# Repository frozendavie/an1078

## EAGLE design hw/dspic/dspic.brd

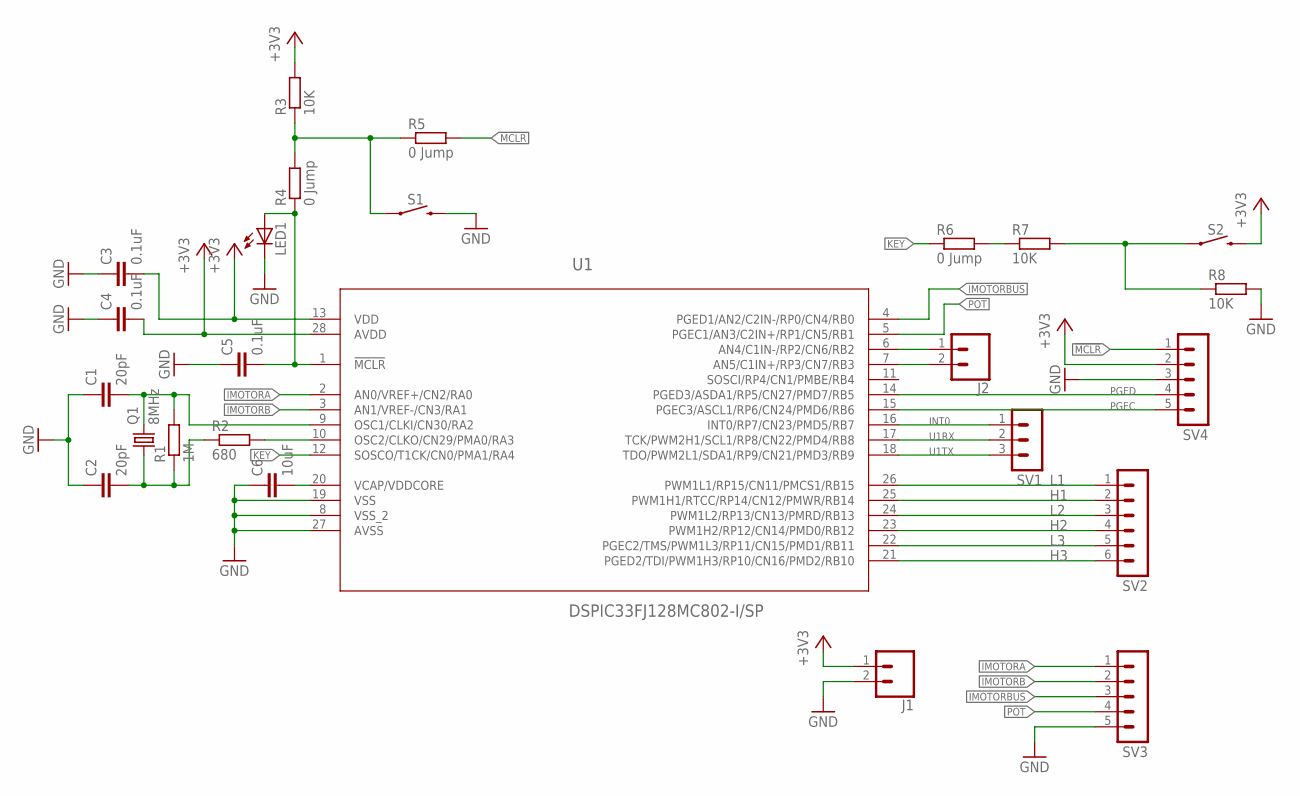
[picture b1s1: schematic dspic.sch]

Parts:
C1, C2: 20pF; C025-024X044
C3, C4, C5: 0.1uF; C025-024X044
C6: 10uF; C025-024X044
J1, J2: CONN_02; 1X02
LED1: LED3MM
Q1: 8MHz; HC49/S
R1: 1M; 0207/10
R2: 680; 0207/10
R3, R7, R8: 10K; 0207/10
R4, R5, R6: 0 Jump; 0207/10
S1, S2: MOMENTARY-SWITCH-SPST-PTH-6.0MM; TACTILE_SWITCH_PTH_6.0MM
SV1: MA03-1
SV2: MA06-1
SV3, SV4: MA05-1
U1: DSPIC33FJ128MC802-I/SP; DIP254P762X508-28

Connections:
!MCLR!: R5.2, SV4.1
+3V3: C3.2, C4.2, J1.1, R3.2, S2.3 (2), SV4.2, U1.13 (VDD), U1.28 (AVDD)
GND: C1.1, C2.1, C3.1, C4.1, C5.1, C6.1, J1.2, LED1.K (C), R8.2, S1.3 (2), SV3.5, SV4.3, U1.8 (VSS_2), U1.19 (VSS), U1.27 (AVSS)
H1: SV2.2, U1.25 (PWM1H1/RTCC/RP14/CN12/PMWR/RB14)
H2: SV2.4, U1.23 (PWM1H2/RP12/CN14/PMD0/RB12)
H3: SV2.6, U1.21 (PGED2/TDI/PWM1H3/RP10/CN16/PMD2/RB10)
IMOTORA: SV3.1, U1.2 (AN0/VREF+/CN2/RA0)
IMOTORB: SV3.2, U1.3 (AN1/VREF-/CN3/RA1)
IMOTORBUS: SV3.3, U1.4 (PGED1/AN2/C2IN-/RP0/CN4/RB0)
INT0: SV1.1, U1.16 (INT0/RP7/CN23/PMD5/RB7)
KEY: R6.1, U1.12 (SOSCO/T1CK/CN0/PMA1/RA4)
L1: SV2.1, U1.26 (PWM1L1/RP15/CN11/PMCS1/RB15)
L2: SV2.3, U1.24 (PWM1L2/RP13/CN13/PMRD/RB13)
L3: SV2.5, U1.22 (PGEC2/TMS/PWM1L3/RP11/CN15/PMD1/RB11)
unnamed: C6.2, U1.20 (VCAP/VDDCORE)
unnamed: C5.2, LED1.A, R4.1, U1.1 (!MCLR!)
unnamed: R7.2, R8.1, S2.1
unnamed: R3.1, R4.2, R5.1, S1.1
unnamed: R6.2, R7.1
unnamed: C1.2, Q1.2, R1.2, U1.9 (OSC1/CLKI/CN30/RA2)
unnamed: C2.2, Q1.1, R1.1, R2.1
unnamed: R2.2, U1.10 (OSC2/CLKO/CN29/PMA0/RA3)
unnamed: J2.1, U1.6 (AN4/C1IN-/RP2/CN6/RB2)
unnamed: J2.2, U1.7 (AN5/C1IN+/RP3/CN7/RB3)
PGEC: SV4.5, U1.15 (PGEC3/ASCL1/RP6/CN24/PMD6/RB6)
PGED: SV4.4, U1.14 (PGED3/ASDA1/RP5/CN27/PMD7/RB5)
POT: SV3.4, U1.5 (PGEC1/AN3/C2IN+/RP1/CN5/RB1)
U1RX: SV1.2, U1.17 (TCK/PWM2H1/SCL1/RP8/CN22/PMD4/RB8)
U1TX: SV1.3, U1.18 (TDO/PWM2L1/SDA1/RP9/CN21/PMD3/RB9)

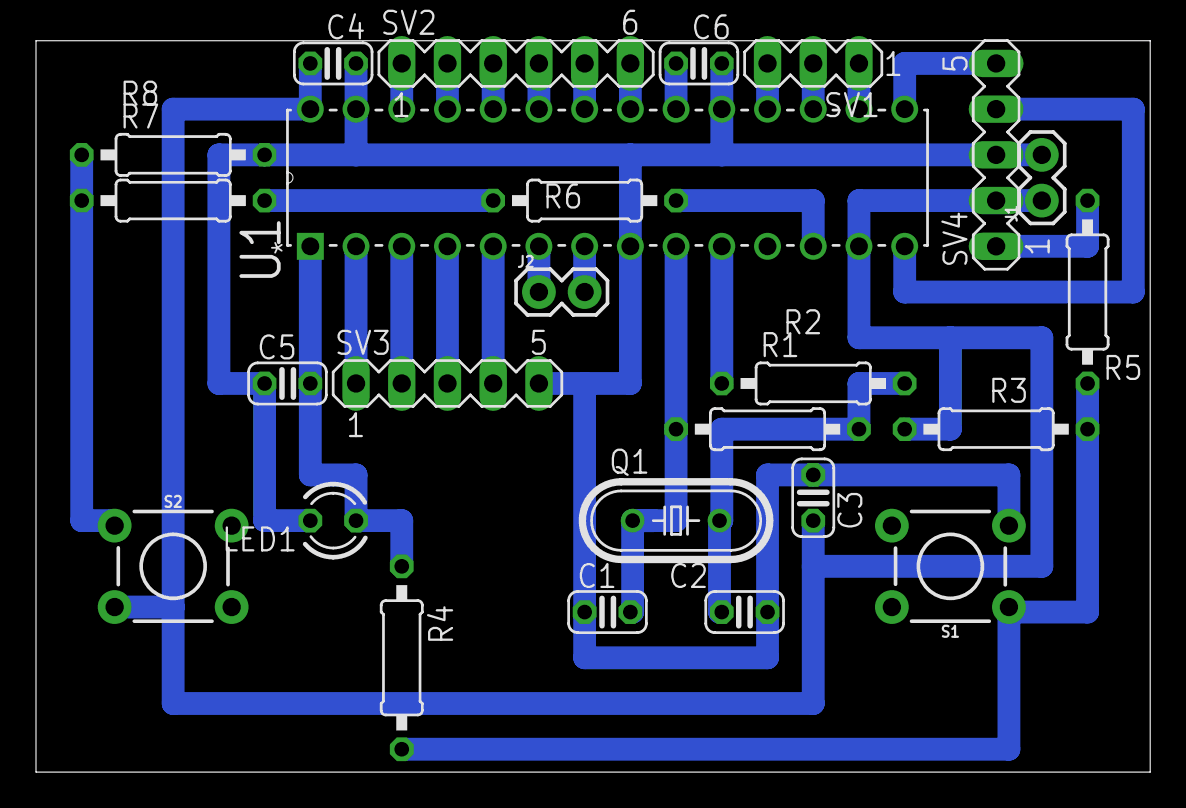
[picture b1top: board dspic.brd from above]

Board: 2 copper layers, 61.9 x 40.6 mm, 25 parts (0 on the bottom side), 29 nets.

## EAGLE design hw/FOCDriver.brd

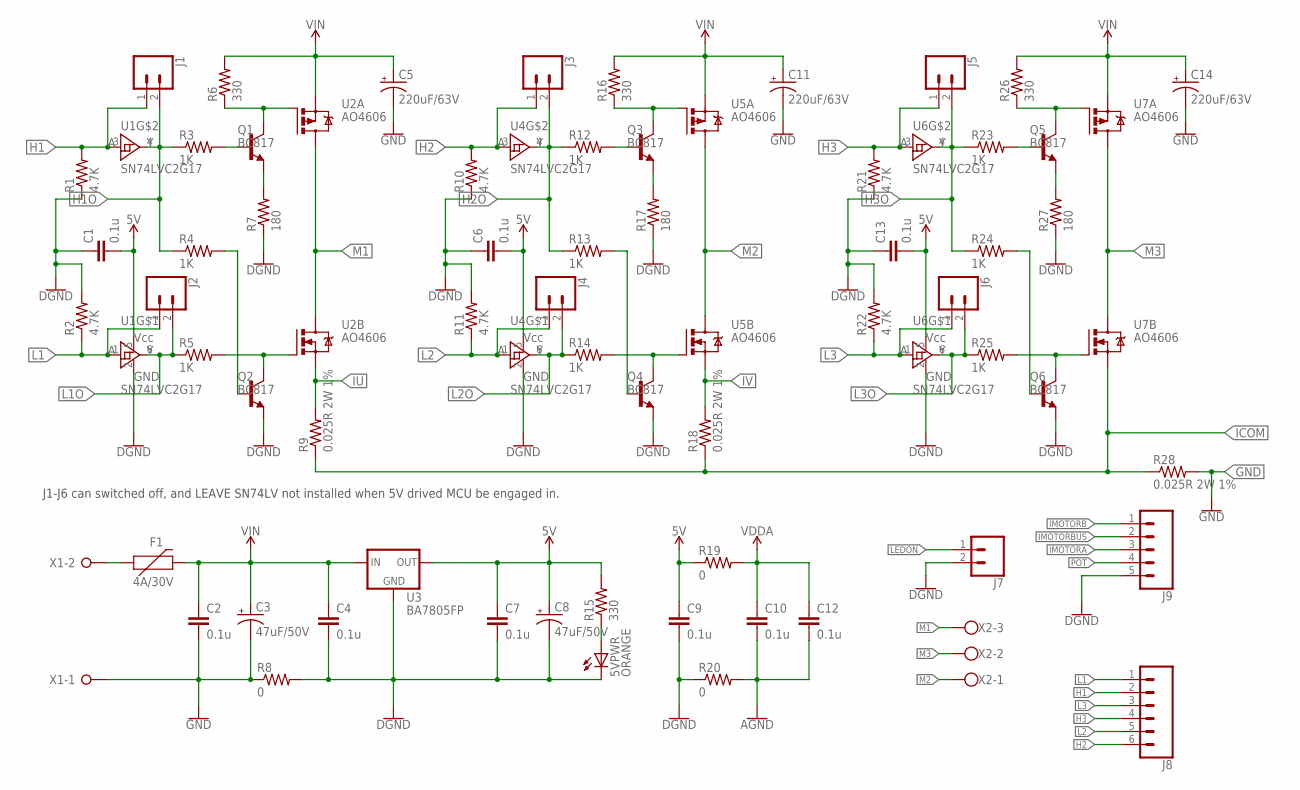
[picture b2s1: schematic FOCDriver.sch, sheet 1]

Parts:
5VPWR: ORANGE; SML0805
C1, C2, C4, C6, C7, C9, C10, C12, C13: 0.1u; C0805
C3, C8: 47uF/50V; E2,5-7
C5, C11, C14: 220uF/63V; E5-10,5
F1: 4A/30V; PTH
J1, J2, J3, J4, J5, J6, J7: CONN_02; 1X02
J8: CONN_06SILK_FEMALE_PTH; 1X06
J9: CONN_05; 1X05
Q1, Q2, Q3, Q4, Q5, Q6: BC817; SOT23-BEC
R1, R2, R10, R11, R21, R22: 4.7K; R0805
R3, R4, R5, R12, R13, R14, R23, R24, R25: 1K; R0805
R6, R15, R16, R26: 330; R0805
R7, R17, R27: 180; R0805
R8, R19, R20: 0; R0805
R9, R18, R28: 0.025R 2W 1%; R2512
U1, U4, U6: SN74LVC2G17; SOT23-6
U2, U5, U7: AO4606; SO08
U3: BA7805FP; TO-252
X1: W237-02P; W237-132
X2: W237-103

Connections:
5V: C1.2, C6.2, C7.1, C8.+, C9.1, C13.2, R15.2, R19.1, U1.5 (VCC), U3.2 (OUT), U4.5 (VCC), U6.5 (VCC); also elsewhere on the board
AGND: C10.2, C12.2, R20.2; also elsewhere on the board
DGND: 5VPWR.C, C1.1, C4.2, C6.1, C7.2, C8.-, C9.2, C13.1, J7.2, J9.5, Q2.E, Q4.E, Q6.E, R1.1, R2.2, R7.1, R8.2, R10.1, R11.2, R17.1, R20.1, R21.1, R22.2, R27.1, U1.2 (GND), U3.3 (GND), U4.2 (GND), U6.2 (GND); also elsewhere on the board
GND: C2.2, C3.-, C5.-, C11.-, C14.-, R8.1, R28.2, X1.1; also elsewhere on the board
H1: J1.1, J8.2, R1.2, U1.3 (A)
H1O: J1.2, R3.1, R4.1, U1.4 (Y); also elsewhere on the board
H2: J3.1, J8.6, R10.2, U4.3 (A)
H2O: J3.2, R12.1, R13.1, U4.4 (Y); also elsewhere on the board
H3: J5.1, J8.4, R21.2, U6.3 (A)
H3O: J5.2, R23.1, R24.1, U6.4 (Y); also elsewhere on the board
ICOM: R9.1, R18.1, R28.1, U7.1 (S); also elsewhere on the board
IMOTORA: J9.3; also elsewhere on the board
IMOTORB: J9.1; also elsewhere on the board
IMOTORBUS: J9.2; also elsewhere on the board
IU: R9.2, U2.1 (S); also elsewhere on the board
IV: R18.2, U5.1 (S); also elsewhere on the board
L1: J2.1, J8.1, R2.1, U1.1 (A)
L1O: J2.2, R5.1, U1.6 (Y); also elsewhere on the board
L2: J4.1, J8.5, R11.1, U4.1 (A)
L2O: J4.2, R14.1, U4.6 (Y); also elsewhere on the board
L3: J6.1, J8.3, R22.1, U6.1 (A)
L3O: J6.2, R25.1, U6.6 (Y); also elsewhere on the board
LEDON: J7.1; also elsewhere on the board
M1: U2.5 (D), U2.6 (D), U2.7 (D), U2.8 (D), X2.3
M2: U5.5 (D), U5.6 (D), U5.7 (D), U5.8 (D), X2.1
M3: U7.5 (D), U7.6 (D), U7.7 (D), U7.8 (D), X2.2
unnamed: Q6.C, R25.2, U7.2 (G)
unnamed: F1.P$1 (1), X1.2
unnamed: Q5.C, R26.1, U7.4 (G)
unnamed: Q4.C, R14.2, U5.2 (G)
unnamed: Q3.C, R16.1, U5.4 (G)
unnamed: Q2.C, R5.2, U2.2 (G)
unnamed: Q1.C, R6.1, U2.4 (G)
unnamed: Q5.E, R27.2
unnamed: Q1.B, R3.2
unnamed: 5VPWR.A, R15.1
unnamed: Q2.B, R4.2
unnamed: Q3.B, R12.2
unnamed: Q1.E, R7.2
unnamed: Q4.B, R13.2
unnamed: Q5.B, R23.2
unnamed: Q3.E, R17.2
unnamed: Q6.B, R24.2
POT: J9.4; also elsewhere on the board
VDDA: C10.1, C12.1, R19.2; also elsewhere on the board
VIN: C2.1, C3.+, C4.1, C5.+, C11.+, C14.+, F1.P$2 (2), R6.2, R16.2, R26.2, U2.3 (S), U3.1 (IN), U5.3 (S), U7.3 (S)

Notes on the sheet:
J1-J6 can switched off, and LEAVE SN74LV not installed when 5V drived MCU be engaged in.

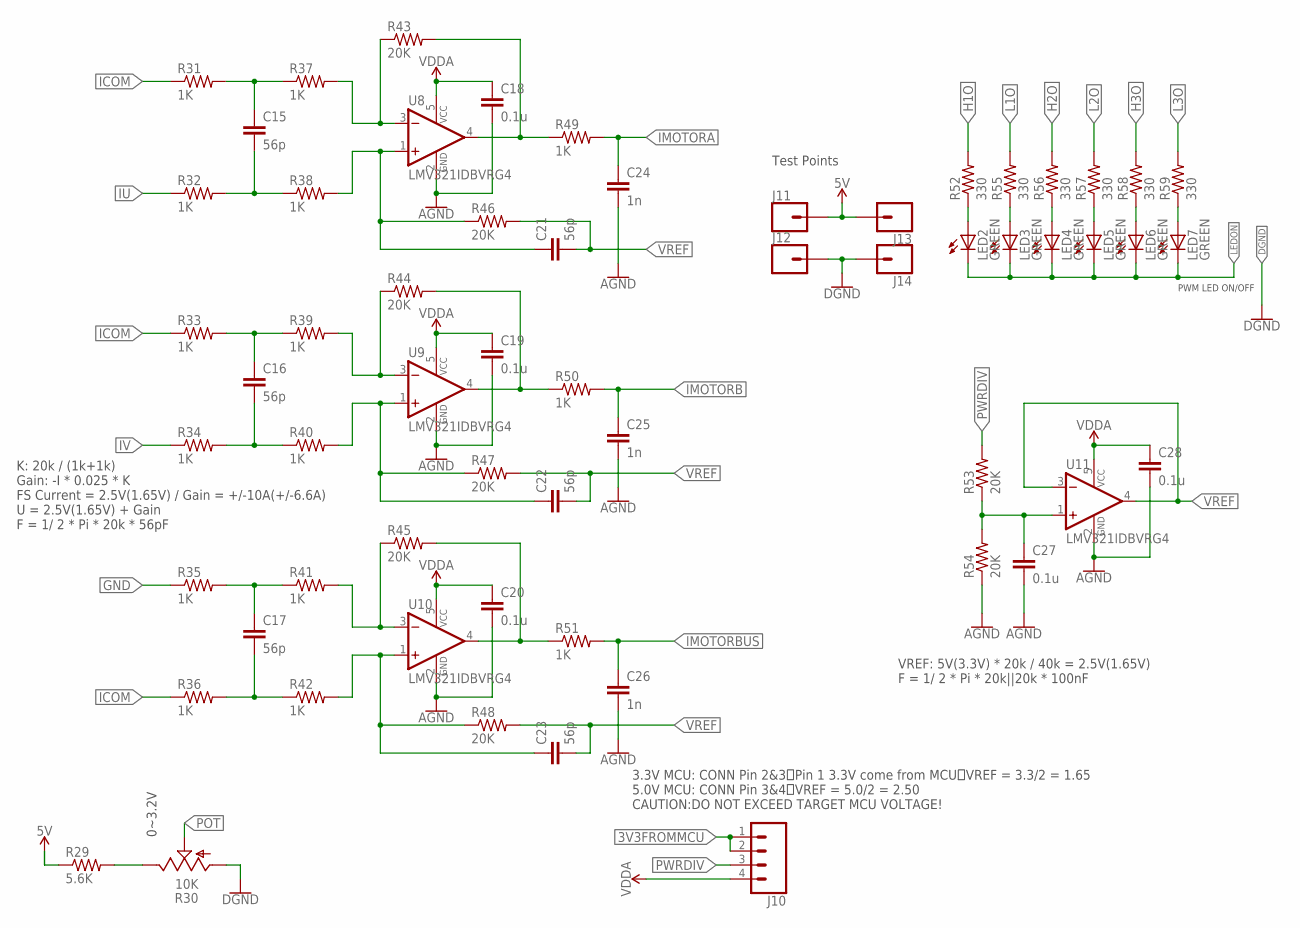
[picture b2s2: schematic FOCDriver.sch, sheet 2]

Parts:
C15, C16, C17, C21, C22, C23: 56p; C0805
C18, C19, C20, C27, C28: 0.1u; C0805
C24, C25, C26: 1n; C0805
J10: CONN_04; 1X04
J11, J12, J13, J14: CONN_01PTH_NO_SILK_YES_STOP; 1X01_NO_SILK
LED2, LED3, LED4, LED5, LED6, LED7: GREEN; SML0805
R29: 5.6K; R0805
R30: 10K; CT6
R31, R32, R33, R34, R35, R36, R37, R38, R39, R40, R41, R42, R49, R50, R51: 1K; R0805
R43, R44, R45, R46, R47, R48, R53, R54: 20K; R0805
R52, R55, R56, R57, R58, R59: 330; R0805
U8, U9, U10, U11: LMV321IDBVRG4; SOT95P285X120-5N

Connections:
3V3FROMMCU: J10.1, J10.2
5V: J11.1, J13.1, R29.1; also elsewhere on the board
AGND: C18.2, C19.2, C20.2, C24.2, C25.2, C26.2, C27.2, C28.2, R54.1, U8.2 (GND), U9.2 (GND), U10.2 (GND), U11.2 (GND); also elsewhere on the board
DGND: J12.1, J14.1, R30.A; also elsewhere on the board
GND: R35.1; also elsewhere on the board
H1O: R52.2; also elsewhere on the board
H2O: R56.2; also elsewhere on the board
H3O: R58.2; also elsewhere on the board
ICOM: R31.1, R33.1, R36.1; also elsewhere on the board
IMOTORA: C24.1, R49.2; also elsewhere on the board
IMOTORB: C25.1, R50.2; also elsewhere on the board
IMOTORBUS: C26.1, R51.2; also elsewhere on the board
IU: R32.1; also elsewhere on the board
IV: R34.1; also elsewhere on the board
L1O: R55.2; also elsewhere on the board
L2O: R57.2; also elsewhere on the board
L3O: R59.2; also elsewhere on the board
LEDON: LED2.C, LED3.C, LED4.C, LED5.C, LED6.C, LED7.C; also elsewhere on the board
unnamed: R29.2, R30.E
unnamed: C15.1, R31.2, R37.1
unnamed: C15.2, R32.2, R38.1
unnamed: R37.2, R43.1, U8.3 (-IN)
unnamed: C16.1, R33.2, R39.1
unnamed: C21.1, R38.2, R46.1, U8.1 (+IN)
unnamed: R43.2, R49.1, U8.4 (OUT)
unnamed: C16.2, R34.2, R40.1
unnamed: C27.1, R53.1, R54.2, U11.1 (+IN)
unnamed: R39.2, R44.1, U9.3 (-IN)
unnamed: C22.1, R40.2, R47.1, U9.1 (+IN)
unnamed: R44.2, R50.1, U9.4 (OUT)
unnamed: C17.1, R35.2, R41.1
unnamed: C17.2, R36.2, R42.1
unnamed: R41.2, R45.1, U10.3 (-IN)
unnamed: C23.1, R42.2, R48.1, U10.1 (+IN)
unnamed: R45.2, R51.1, U10.4 (OUT)
unnamed: LED2.A, R52.1
unnamed: LED3.A, R55.1
unnamed: LED4.A, R56.1
unnamed: LED5.A, R57.1
unnamed: LED6.A, R58.1
unnamed: LED7.A, R59.1
POT: R30.S; also elsewhere on the board
PWRDIV: J10.3, R53.2
VDDA: C18.1, C19.1, C20.1, C28.1, J10.4, U8.5 (VCC), U9.5 (VCC), U10.5 (VCC), U11.5 (VCC); also elsewhere on the board
VREF: C21.2, C22.2, C23.2, R46.2, R47.2, R48.2, U11.3 (-IN), U11.4 (OUT)

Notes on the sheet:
K: 20k / (1k+1k) Gain: -I * 0.025 * K FS Current = 2.5V(1.65V) / Gain = +/-10A(+/-6.6A) U = 2.5V(1.65V) + Gain F = 1/ 2 * Pi * 20k * 56pF
VREF: 5V(3.3V) * 20k / 40k = 2.5V(1.65V) F = 1/ 2 * Pi * 20k||20k * 100nF
0~3.2V
PWM LED ON/OFF
3.3V MCU: CONN Pin 2&3，Pin 1 3.3V come from MCU，VREF = 3.3/2 = 1.65 5.0V MCU: CONN Pin 3&4，VREF = 5.0/2 = 2.50 CAUTION:DO NOT EXCEED TARGET MCU VOLTAGE!
Test Points

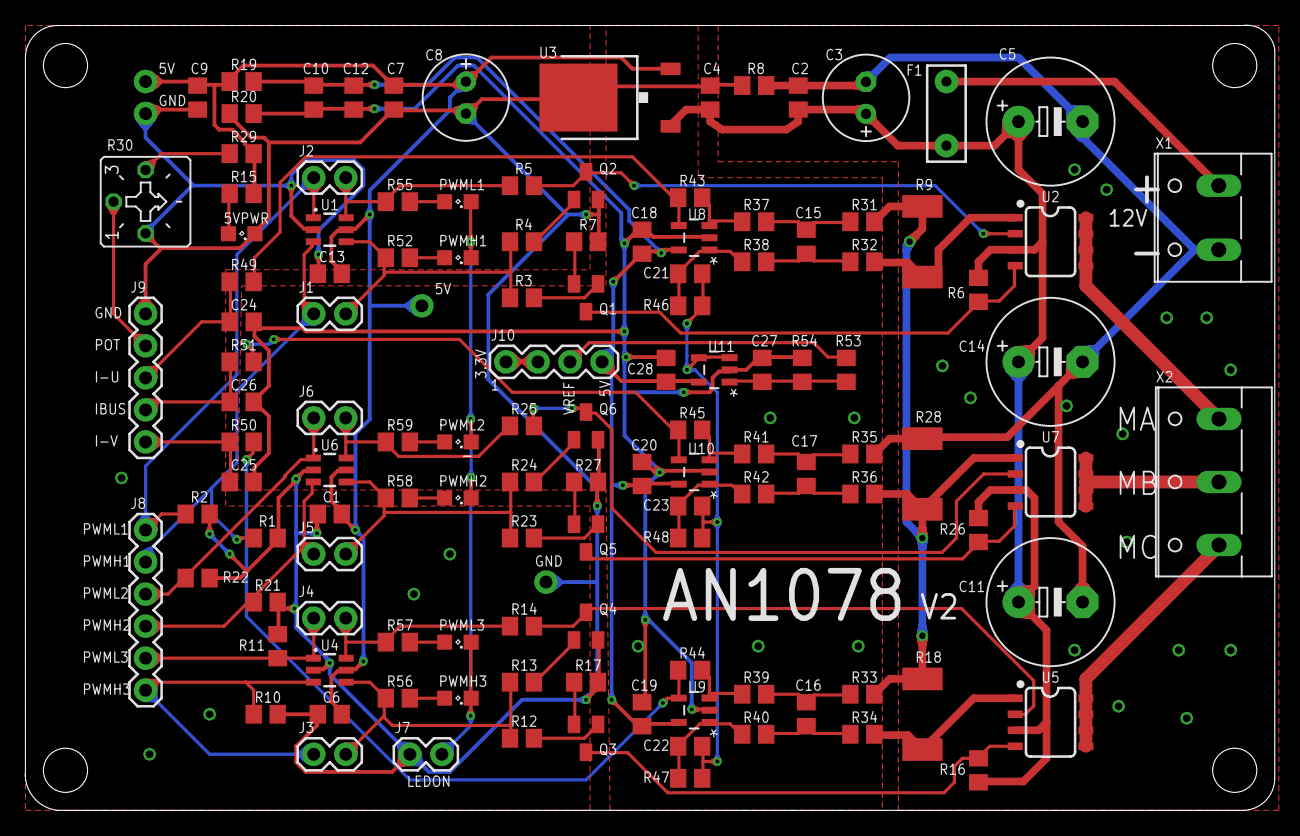
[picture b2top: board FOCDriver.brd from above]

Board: 2 copper layers, 99.1 x 62.3 mm, 128 parts (0 on the bottom side), 72 nets.

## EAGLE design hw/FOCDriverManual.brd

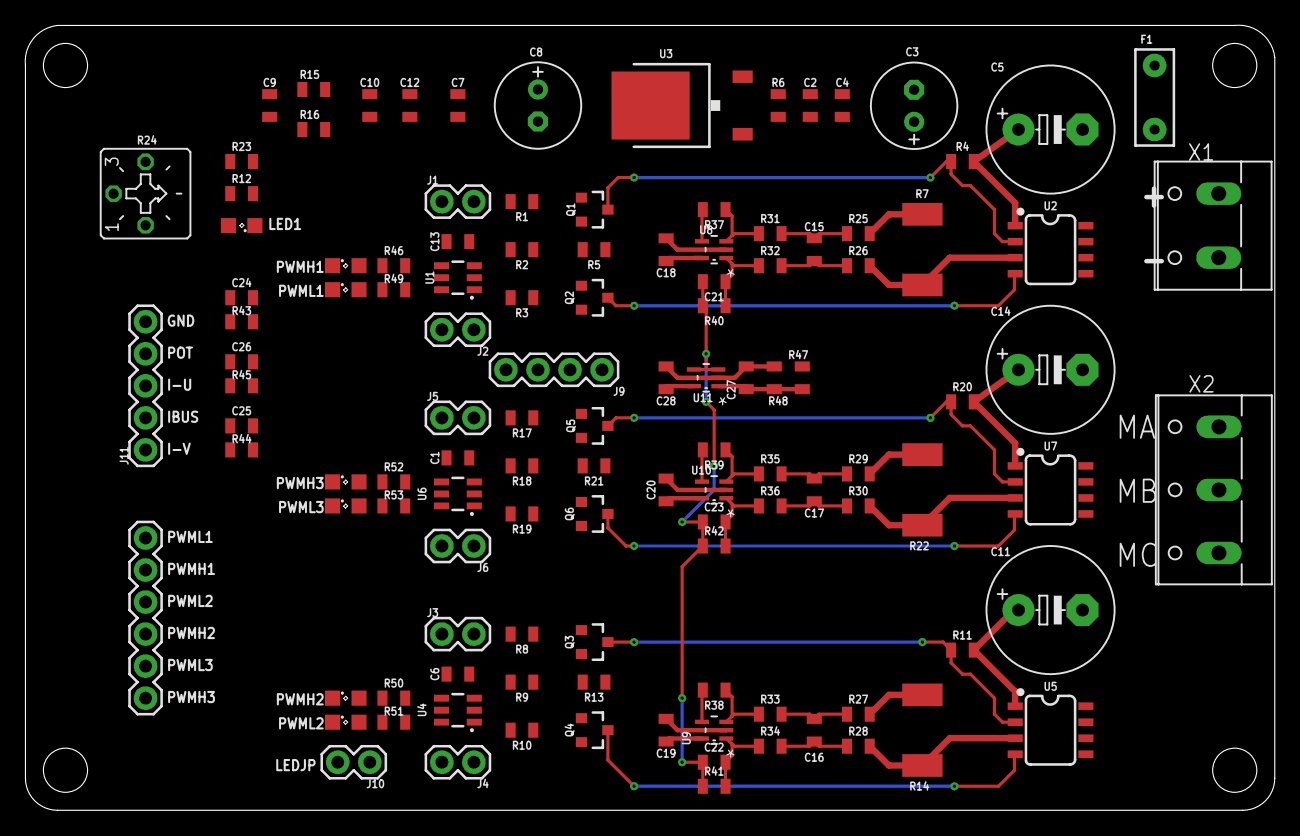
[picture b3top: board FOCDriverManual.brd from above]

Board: 2 copper layers, 99.1 x 62.2 mm, 118 parts (0 on the bottom side), 72 nets.

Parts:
C1, C2, C4, C6, C7, C9, C10, C12, C13, C18, C19, C20, C27, C28: 0.1uF; 0805
C3, C8: 47uF/50V; E2,5-7
C5, C11, C14: 220uF/63V; E5-10,5
C15, C16, C17: 56pF; 0805
C21, C22, C23: 100pF; 0805
C24, C25, C26: 1nF; 0805
F1: 4A/30V; PTH
J1, J2, J3, J4, J5, J6, J10: 1X02
J8: 1X06
J9: 1X04
J11: 1X05
LED1: ORANGE; SML0805
LED2, LED3, LED4, LED5, LED6, LED7: GREEN; SML0805
Q1, Q2, Q3, Q4, Q5, Q6: BC817; SOT23-3
R1, R2, R3, R8, R9, R10, R17, R18, R19: 1K; 0805
R4, R11, R12, R20: 330; 0805
R5, R13, R21: 180; 0805
R6, R16: 0R; 0805
R7, R14, R22: 0.025R 2W 1%; R2512
R15: 1R; 0805
R23: 5.6K; 0805
R24: 10K; CT6
R25, R26, R27, R28, R29, R30, R31, R32, R33, R34, R35, R36, R43, R44, R45: 1K 1%; 0805
R37, R38, R39, R40, R41, R42, R47, R48: 10K 1%; 0805
R46, R49, R50, R51, R52, R53: 220; 0805
U1, U4, U6: SN74LVC2G17; SOT23-6
U2, U5, U7: AO4606; SO08
U3: BA7805FP; TO-252
U8, U9, U10, U11: LMV321SQ3T2G; SOT65P210X110-5N
X1: W237-132
X2: W237-103

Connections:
3V3FROMMCU: J9.1, J9.2
5V: C1.1, C6.1, C7.1, C8.+, C9.1, C13.1, R12.2, R15.1, R23.2, U1.5, U3.2, U4.5, U6.5
AGND: C10.2, C12.2, C18.2, C19.2, C20.2, C24.2, C25.2, C26.2, C27.2, C28.2, R16.2, R48.1, U8.2, U9.2, U10.2, U11.2
DGND: C1.2, C4.2, C6.2, C7.2, C8.-, C9.2, C13.2, J10.2, J11.5, LED1.C, Q2.2, Q4.2, Q6.2, R5.1, R6.2, R13.1, R16.1, R21.1, R24.A, U1.2, U3.3, U4.2, U6.2
GND: C2.2, C3.-, C5.-, C11.-, C14.-, R6.1, R22.2, R29.1, X1.1
H1: J1.1, J8.2, U1.3
H1O: J1.2, R1.1, R2.1, R46.2, U1.4
H2: J3.1, J8.6, U4.3
H2O: J3.2, R8.1, R9.1, R50.2, U4.4
H3: J5.1, J8.4, U6.3
H3O: J5.2, R17.1, R18.1, R52.2, U6.4
ICOM: R7.1, R14.1, R22.1, R25.1, R27.1, R30.1, U7.3
IMOTORA: C24.1, J11.3, R43.2
IMOTORB: C25.1, J11.1, R44.2
IMOTORBUS: C26.1, J11.2, R45.2
IU: R7.2, R26.1, U2.3
IV: R14.2, R28.1, U5.3
L1: J2.1, J8.1, U1.1
L1O: J2.2, R3.1, R49.2, U1.6
L2: J4.1, J8.5, U4.1
L2O: J4.2, R10.1, R51.2, U4.6
L3: J6.1, J8.3, U6.1
L3O: J6.2, R19.1, R53.2, U6.6
LEDJP1: J10.1, LED2.C, LED3.C, LED4.C, LED5.C, LED6.C, LED7.C
M1: U2.5, U2.6, U2.7, U2.8, X2.3
M2: U5.5, U5.6, U5.7, U5.8, X2.1
M3: U7.5, U7.6, U7.7, U7.8, X2.2
unnamed: Q6.3, R19.2, U7.4
unnamed: R23.1, R24.E
unnamed: F1.P$1, X1.2
unnamed: Q5.3, R20.1, U7.2
unnamed: Q4.3, R10.2, U5.4
unnamed: Q3.3, R11.1, U5.2
unnamed: Q2.3, R3.2, U2.4
unnamed: Q1.3, R4.1, U2.2
unnamed: C15.1, R25.2, R31.1
unnamed: C15.2, R26.2, R32.1
unnamed: R31.2, R37.1, U8.3
unnamed: C16.1, R27.2, R33.1
unnamed: C21.2, R32.2, R40.1, U8.1
unnamed: R37.2, R43.1, U8.4
unnamed: C16.2, R28.2, R34.1
unnamed: C27.1, R47.1, R48.2, U11.1
unnamed: R33.2, R38.1, U9.3
unnamed: C22.2, R34.2, R41.1, U9.1
unnamed: R38.2, R44.1, U9.4
unnamed: C17.1, R29.2, R35.1
unnamed: C17.2, R30.2, R36.1
unnamed: R35.2, R39.1, U10.3
unnamed: C23.2, R36.2, R42.1, U10.1
unnamed: R39.2, R45.1, U10.4
unnamed: Q5.2, R21.2
unnamed: Q1.1, R1.2
unnamed: LED1.A, R12.1
unnamed: Q2.1, R2.2
unnamed: LED2.A, R46.1
unnamed: LED3.A, R49.1
unnamed: LED4.A, R50.1
unnamed: LED5.A, R51.1
unnamed: LED6.A, R52.1
unnamed: LED7.A, R53.1
unnamed: Q3.1, R8.2
unnamed: Q1.2, R5.2
unnamed: Q4.1, R9.2
unnamed: Q5.1, R17.2
unnamed: Q3.2, R13.2
unnamed: Q6.1, R18.2
POT: J11.4, R24.S
PWRDIV: J9.3, R47.2
VDDA: C10.1, C12.1, C18.1, C19.1, C20.1, C28.1, J9.4, R15.2, U8.5, U9.5, U10.5, U11.5
VIN: C2.1, C3.+, C4.1, C5.+, C11.+, C14.+, F1.P$2, R4.2, R11.2, R20.2, U2.1, U3.1, U5.1, U7.1
VREF: C21.1, C22.1, C23.1, R40.2, R41.2, R42.2, U11.3, U11.4

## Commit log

2017-03-10 init code
2017-03-10 update app note
2017-03-10 move app note to doc
2017-03-10 format
2017-03-11 reformat
2017-03-11 reconfig project
2017-03-12 add hw
2017-03-12 update sch
2017-03-13 layout pcb elements
2017-03-13 auto layout
2017-03-14 layout
2017-03-17 layout, add doc
2017-03-17 convert to windows format
2017-03-20 packages
2017-03-20 ignore txt
2017-03-21 add resettable fuse
2017-03-21 trans
2017-03-21 layout trans driver
2017-03-22 simulation
2017-03-23 branch irf9389
2017-03-23 change mosfet chip
2017-03-27 change power conn
2017-03-29 change lm258
2017-03-29 LMV321
2017-03-30 back half manual layout brd
2017-03-31 add info silk
2017-03-31 branch to C version
2017-04-01 correct op gain
2017-04-01 add opamp sim
2017-04-03 add some docs
2017-04-04 refine top silk
2017-04-15 fix error
2017-04-16 fix layout bugs
2017-04-16 fix layout errors
2017-04-17 normal fix
2017-04-17 gerber for product
2017-04-23 new lpc port
2017-04-23 lpc54102 port
2017-04-23 add onboard pins doc
2017-04-23 ignore examples
2017-04-23 ignore examples and remove lib
2017-04-23 pin map docs
2017-04-23 ignore debug config
2017-04-25 set configuration bits
2017-04-26 add dspic files to lpc54102 projects for ref
2017-04-27 dspic
2017-04-27 dspic brd
2017-04-29 config
2017-04-29 config bits
2017-04-29 renew settings
2017-04-30 modified pin settings
2017-05-01 gain
2017-05-01 dmci
2017-05-02 redefine some params
2017-05-02 first run
2017-05-03 tune params
2017-05-04 refine params
2017-05-04 params
2017-05-05 cordic

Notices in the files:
parts and their libraries:
SparkFun-Connectors: Licensing: Creative Commons ShareAlike 4.0 International - https://creativecommons.org/licenses/by-sa/4.0
